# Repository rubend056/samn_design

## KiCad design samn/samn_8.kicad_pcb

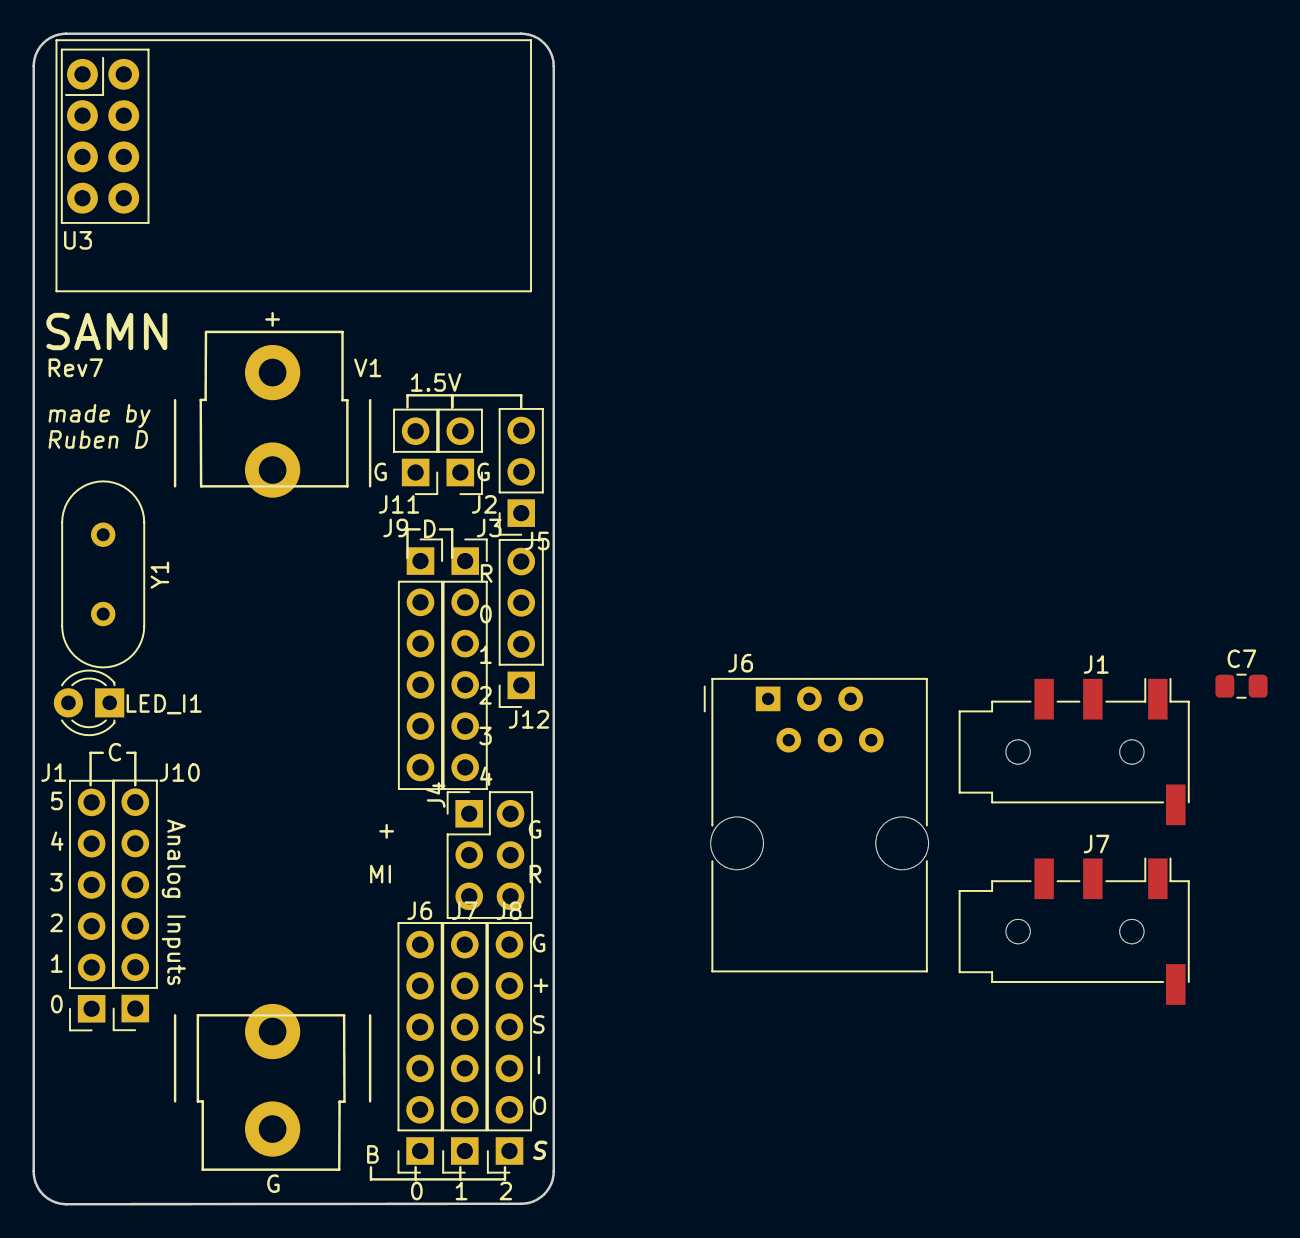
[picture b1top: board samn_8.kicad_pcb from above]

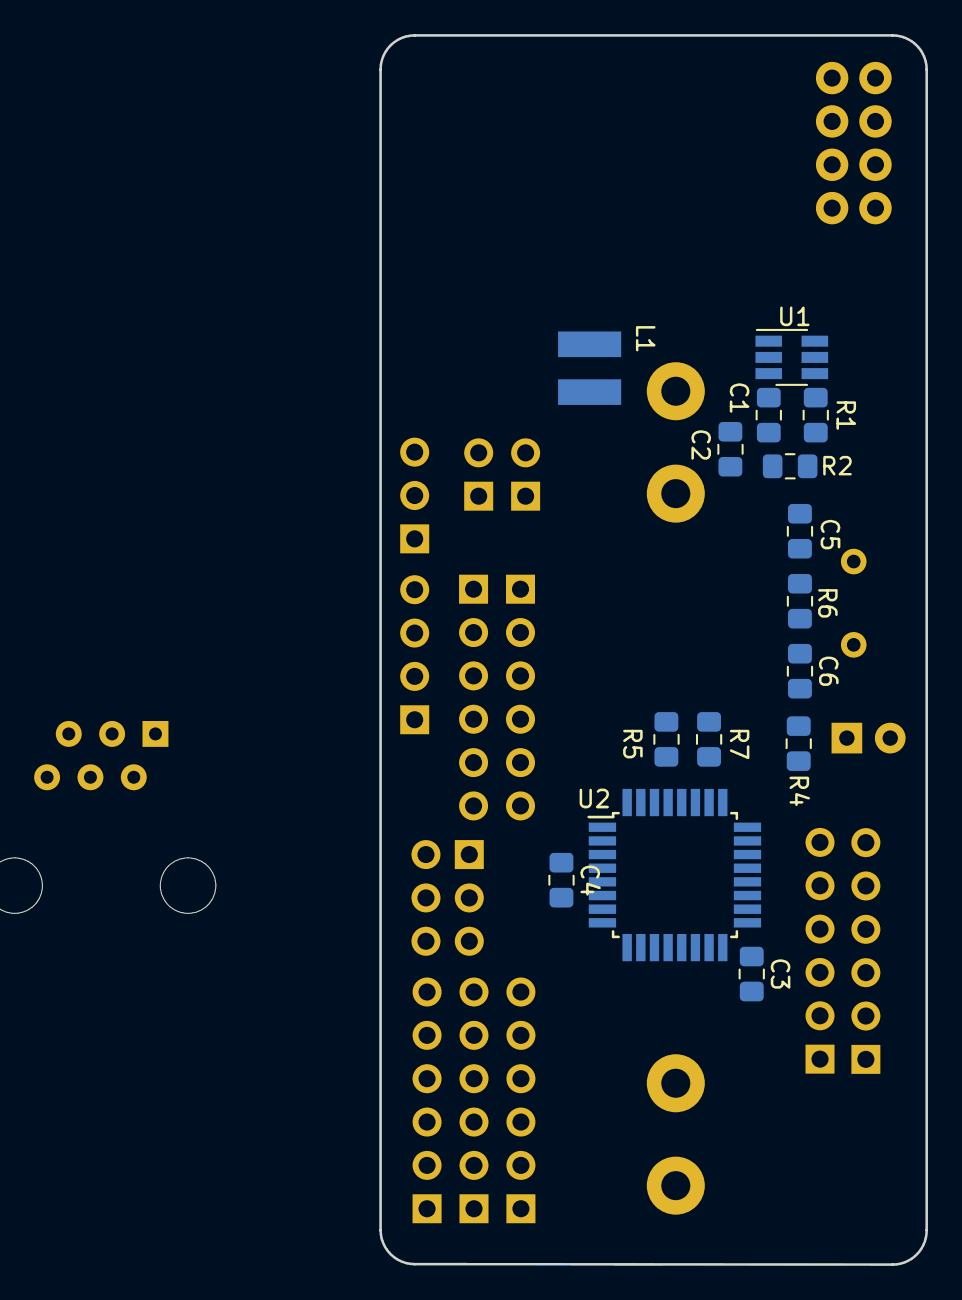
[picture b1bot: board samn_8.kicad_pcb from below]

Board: 2 copper layers, 32.0 x 72.0 mm, 35 parts (15 on the bottom side), 34 nets, no tracks yet.

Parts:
C1: 4.7uF; C_0805_2012Metric_Pad1.15x1.40mm_HandSolder
C2: 10uF; C_0805_2012Metric_Pad1.15x1.40mm_HandSolder
C3, C5, C6: 22pF; C_0805_2012Metric_Pad1.15x1.40mm_HandSolder
C4, C7: 100uF; C_0805_2012Metric_Pad1.15x1.40mm_HandSolder
J1, J7: AudioJack4; Jack_3.5mm_PJ320D_Horizontal
J1#2, J3, J9, J10: Conn_01x06_Female; PinSocket_1x06_P2.54mm_Vertical
J2, J11: Conn_01x02; PinHeader_1x02_P2.54mm_Vertical
J4: Conn_02x03_Male_ICSP; PinHeader_2x03_P2.54mm_Vertical
J5: Conn_01x03; PinSocket_1x03_P2.54mm_Vertical
J6: 6P6C; RJ12_Amphenol_54601
J6#2, J7#2, J8: Conn_01x06; PinSocket_1x06_P2.54mm_Vertical
J12: Conn_01x04; PinSocket_1x04_P2.54mm_Vertical
L1: 4.7uH; NRS4018T4R7MDGJ
LED_I1: 2V 20mA; LED_D3.0mm_FlatTop
R1: 976k; R_0805_2012Metric_Pad1.15x1.40mm_HandSolder
R2: 576k; R_0805_2012Metric_Pad1.15x1.40mm_HandSolder
R4: 200; R_0805_2012Metric_Pad1.15x1.40mm_HandSolder
R5: 5.1k; R_0805_2012Metric_Pad1.15x1.40mm_HandSolder
R6: 1M; R_0805_2012Metric_Pad1.15x1.40mm_HandSolder
R7: 10k; R_0805_2012Metric_Pad1.15x1.40mm_HandSolder
U1: MCP1640BCH; SOT-23-6_Handsoldering
U2: ATmega328PB-AU; TQFP-32_7x7mm_P0.8mm
U3: NRF24L01_Breakout; nRF24L01_Breakout_mine
V1: AA; AA_Holder
Y1: 8MHz; Crystal_HC49-4H_Vertical

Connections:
+1V5: C1.1, J5.2, L1.1, R7.2, U1.3, U1.6
+3V3: C2.2, C4.1, C7.1, J4.5, J6.2, J6#2.5, J7#2.5, J8.5, R1.1, R5.1, U1.5, U2.4, U2.18, U3.2
GND: C1.2, C2.1, C3.1, C4.2, C5.2, C6.2, C7.2, J2.1, J4.1, J6.1, J6#2.6, J7#2.6, J8.6, J11.1, LED_I1.1, R2.2, U1.2, U2.5, U2.21, U3.1, V1.2
MISO: J4.6, J6.4, J6#2.3, J7#2.3, J8.3, U2.16, U3.7
MOSI: J4.3, J6.3, J6#2.2, J7#2.2, J8.2, U2.15, U3.6
unnamed: C3.2, U2.20
unnamed: C5.1, R6.1, U2.7, Y1.1
unnamed: C6.1, R6.2, U2.8, Y1.2
unnamed: J1#2.1, J10.1
unnamed: J1#2.2, J10.2
unnamed: J1#2.3, J10.3
unnamed: J1#2.4, J10.4
unnamed: J1#2.5, J10.5
unnamed: J1#2.6, J10.6
unnamed: J3.2, J9.2, U2.30
unnamed: J3.3, J9.3, U2.31
unnamed: J3.4, J9.4, U2.32, U3.8
unnamed: J3.5, J9.5, U2.1
unnamed: J3.6, J9.6, U2.2
unnamed: J6.6, U2.14
unnamed: J2.2, J5.3, J11.2, V1.1
unnamed: J12.1, U2.22
unnamed: J12.2, U2.19
unnamed: J12.3, U2.6
unnamed: J12.4, U2.3
unnamed: L1.2, U1.1
unnamed: LED_I1.2, R4.1
unnamed: R1.2, R2.1, U1.4
unnamed: R4.2, U2.9
unnamed: R7.1, U2.26
unnamed: U2.10, U3.3
unnamed: U2.11, U3.4
Reset: J3.1, J4.2, J9.1, R5.2, U2.29
SCK: J4.4, J6.5, J6#2.4, J7#2.4, J8.4, U2.17, U3.5

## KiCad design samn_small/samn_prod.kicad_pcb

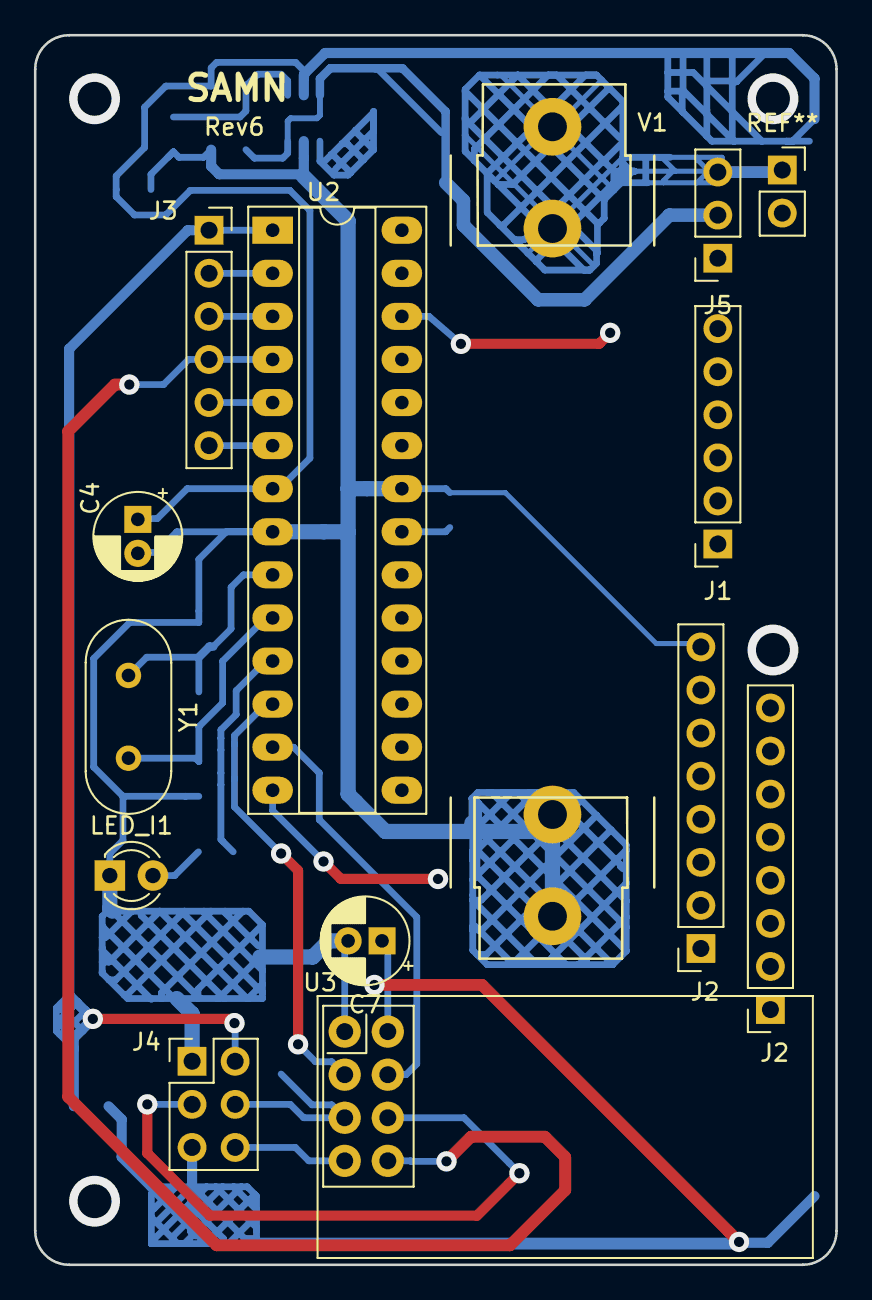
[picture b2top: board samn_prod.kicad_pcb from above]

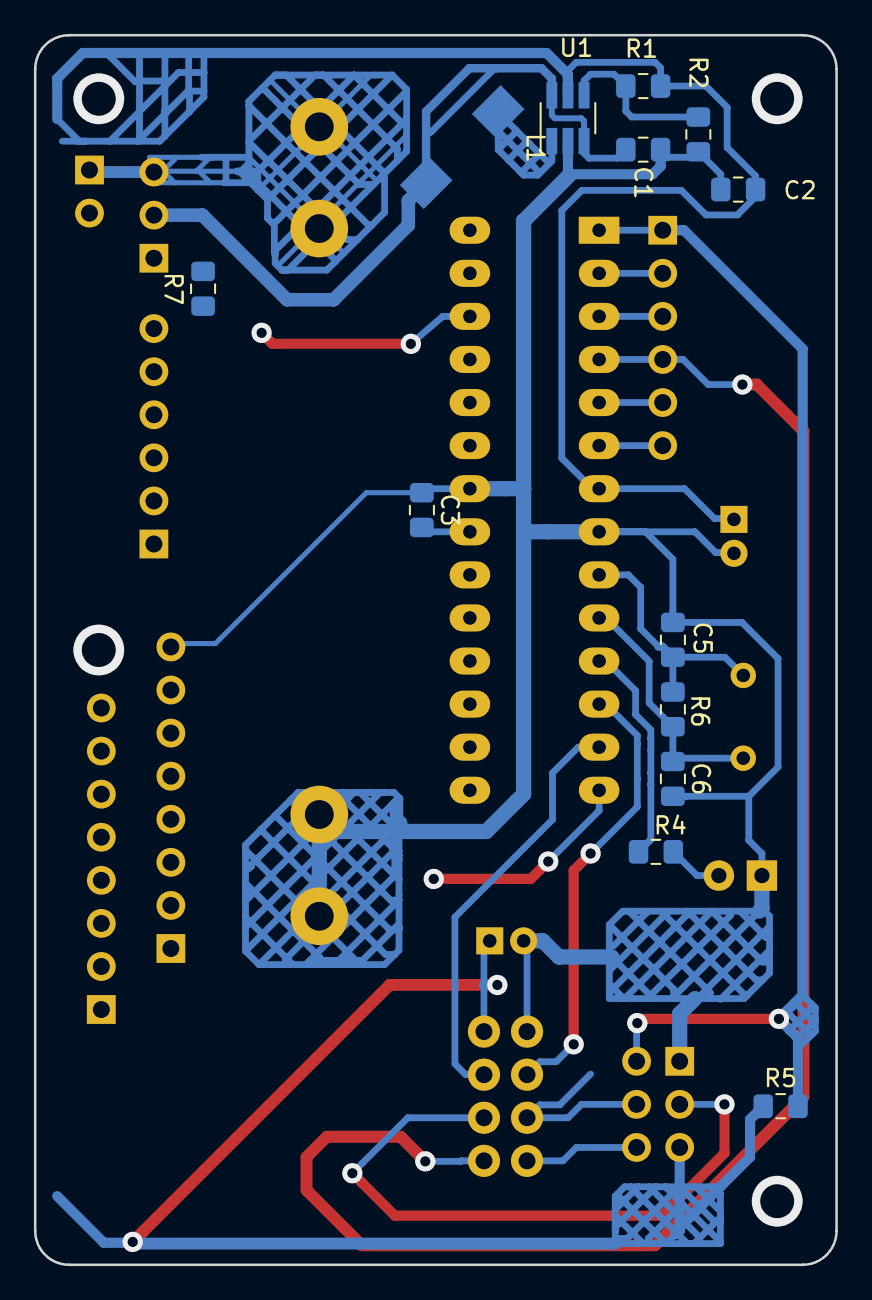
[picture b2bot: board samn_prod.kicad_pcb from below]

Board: 2 copper layers, 47.2 x 72.5 mm, 26 parts (13 on the bottom side), 31 nets.

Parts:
C1: 4.7uF; C_0805_2012Metric_Pad1.15x1.40mm_HandSolder
C2: 10uF; C_0805_2012Metric_Pad1.15x1.40mm_HandSolder
C3, C5, C6: 22pF; C_0805_2012Metric_Pad1.15x1.40mm_HandSolder
C4: 100uF; CP_Radial_D5.0mm_P2.00mm
C7: 47uF; CP_Radial_D5.0mm_P2.00mm
J1, J3: Conn_01x06_Female; PinSocket_1x06_P2.54mm_Vertical
J2, J2#2: Conn_01x08_Female; PinSocket_1x08_P2.54mm_Vertical
J4: Conn_02x03_Male_ICSP; PinHeader_2x03_P2.54mm_Vertical
J5: Conn_01x03; PinSocket_1x03_P2.54mm_Vertical
L1: 4.7uH; SWRH3D16R-4R7NT
LED_I1: 2V 20mA; LED_D3.0mm_FlatTop
R1: 976k; R_0805_2012Metric_Pad1.15x1.40mm_HandSolder
R2: 576k; R_0805_2012Metric_Pad1.15x1.40mm_HandSolder
R4: 200; R_0805_2012Metric_Pad1.15x1.40mm_HandSolder
R5: 5.1k; R_0805_2012Metric_Pad1.15x1.40mm_HandSolder
R6: 1M; R_0805_2012Metric_Pad1.15x1.40mm_HandSolder
R7: 10k; R_0805_2012Metric_Pad1.15x1.40mm_HandSolder
U1: MCP1640BCH; SOT-23-6_Handsoldering
U2: ATmega328-PU; DIP-28_W7.62mm_Socket_LongPads
U3: NRF24L01_Breakout; nRF24L01_Breakout_mine
V1: AA; AA_Holder
Y1: 8MHz; Crystal_HC49-4H_Vertical

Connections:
+1V5: C1.1, J5.2, L1.1, R7.2, U1.3, U1.6
+3V3: C2.2, C4.1, C7.1, J2#2.7, J4.5, R1.1, R5.1, U1.5, U2.7, U2.20, U3.2
GND: C1.2, C2.1, C3.1, C4.2, C5.2, C6.2, C7.2, J2#2.8, J4.1, J5.1, LED_I1.1, R2.2, U1.2, U2.8, U2.22, U3.1, V1.2
MISO: J2#2.5, J4.6, U2.18, U3.7
MOSI: J2#2.4, J4.3, U2.17, U3.6
unnamed: C3.2, U2.21
unnamed: C5.1, R6.1, U2.9, Y1.1
unnamed: C6.1, R6.2, U2.10, Y1.2
unnamed: J1.1, U2.23
unnamed: J1.2, U2.24
unnamed: J1.3, U2.25
unnamed: J1.5, U2.27
unnamed: J1.6, U2.28
unnamed: J2#2.1, U2.14
unnamed: J2#2.2, U2.15
unnamed: J2#2.3, U2.16
unnamed: J3.2, U2.2
unnamed: J3.3, U2.3
unnamed: J3.4, U2.4, U3.8
unnamed: J3.5, U2.5
unnamed: J3.6, U2.6
unnamed: J5.3, V1.1
unnamed: L1.2, U1.1
unnamed: LED_I1.2, R4.1
unnamed: R1.2, R2.1, U1.4
unnamed: R4.2, U2.11
unnamed: R7.1, U2.26
unnamed: U2.12, U3.3
unnamed: U2.13, U3.4
Reset: J3.1, J4.2, R5.2, U2.1
SCK: J2#2.6, J4.4, U2.19, U3.5

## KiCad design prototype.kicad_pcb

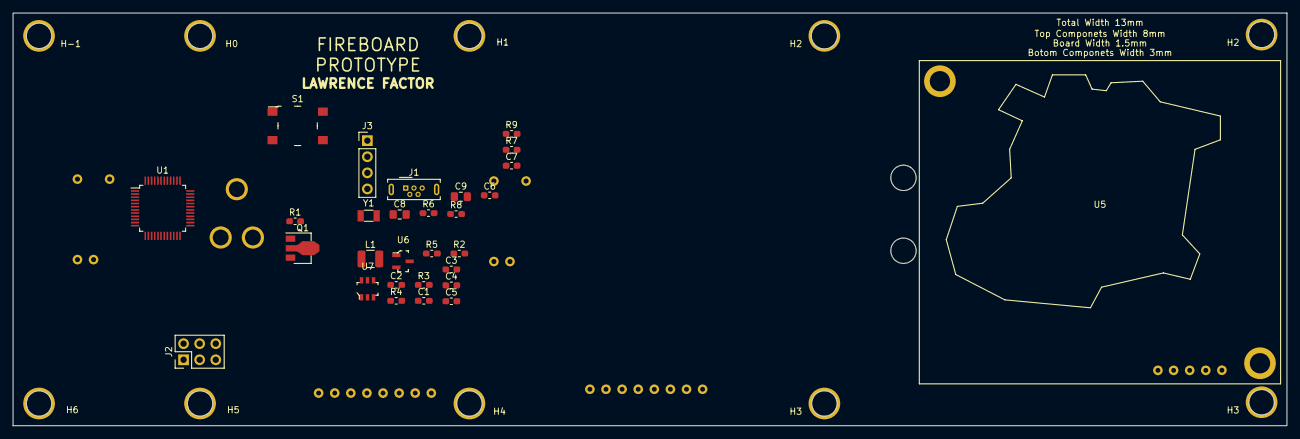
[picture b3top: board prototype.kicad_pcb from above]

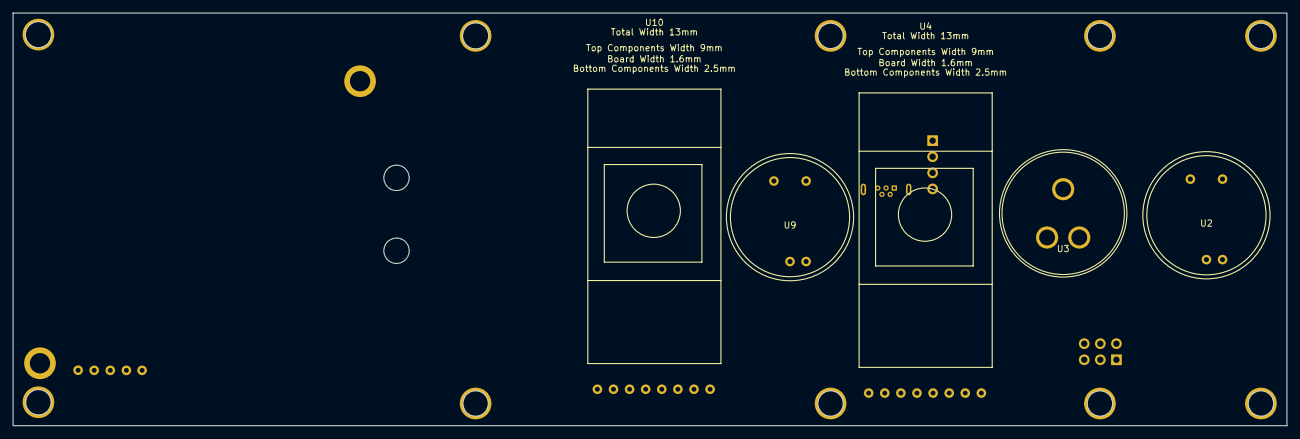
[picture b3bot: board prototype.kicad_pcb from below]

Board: 2 copper layers, 201.0 x 65.1 mm, 44 parts (5 on the bottom side), 32 nets, no tracks yet.

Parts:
C1: 1uF 5V; C_0603_1608Metric_Pad1.05x0.95mm_HandSolder
C2: 10uF 12V; C_0603_1608Metric_Pad1.05x0.95mm_HandSolder
C3: 1uF 3.3V; C_0603_1608Metric_Pad1.05x0.95mm_HandSolder
C4: 10nF 5V; C_0603_1608Metric_Pad1.05x0.95mm_HandSolder
C5: 22uF 5V; C_0603_1608Metric_Pad1.05x0.95mm_HandSolder
C6, C7: 12.5pF; C_0603_1608Metric_Pad1.05x0.95mm_HandSolder
C8, C9: 10uF; C_0805_2012Metric_Pad1.15x1.40mm_HandSolder
H0, H1, H2, H2#2, H3, H3#2, H4, H5, H6: 4mm_hole
H-1: 4mm_hole
J1: USB_B_Micro; USB_Micro-B_Wuerth_614105150721_Vertical
J2: Conn_02x03_Odd_Even; PinHeader_2x03_P2.54mm_Vertical
J3: Link; PinHeader_1x04_P2.54mm_Vertical
L1: 4.7uH; L_1210_3225Metric
Q1: Q_NPN_BCE; SOT-89-3
R1: 330R; R_0603_1608Metric_Pad1.05x0.95mm_HandSolder
R2: 200k; R_0603_1608Metric_Pad1.05x0.95mm_HandSolder
R3: 510k; R_0603_1608Metric_Pad1.05x0.95mm_HandSolder
R4: 47k; R_0603_1608Metric_Pad1.05x0.95mm_HandSolder
R5: 33k; R_0603_1608Metric_Pad1.05x0.95mm_HandSolder
R6, R7: 4.7k; R_0603_1608Metric_Pad1.05x0.95mm_HandSolder
R8: 10k; R_0603_1608Metric_Pad1.05x0.95mm_HandSolder
R9: 22R; R_0603_1608Metric_Pad1.05x0.95mm_HandSolder
S1: KS-01Q-01; Switch_Tactile_SMD_6x6mm_PTS645
U1: ATSAMD21G18A-AUT; TQFP-48_7x7mm_P0.5mm
U2, U9: LOX-02-S
U3: PID-AH
U4, U10: CO
U5: CO2
U6: 3.3V; SOT-23-3
U7: AP3211 Buck; SOT-23-6
Y1: 32.86MHz; Crystal_SMD_3215-2Pin_3.2x1.5mm

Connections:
+5V: C1.1, C5.1, J1.1, J2.2, L1.2, U2.1, U3.1, U6.2, U9.1
+12V: C2.1, J3.2, R3.1, U5.3, U7.5
/PIDGND: Q1.2, U3.3
/PID_on: R1.2, U1.13
/RX0: U1.16, U9.3
/RX1: U1.28, U10.3
/RX2: U1.24, U2.3
/RX3: U1.30, U4.3
/TX0: U1.15, U9.4
/TX1: U1.27, U10.2
/TX2: U1.23, U2.4
/TX3: U1.29, U4.2
D+: J1.3, U1.34
D-: J1.2, U1.33
GND: C1.2, C2.2, C3.2, C5.2, C6.2, C7.2, C8.1, C9.1, J1.5, J1.6, J2.6, J3.1, Q1.3, R2.1, R5.2, S1.2, S1.4, U1.5, U1.18, U1.35, U1.42, U2.2, U4.6, U5.2, U6.1, U7.2, U9.2, U10.6
MISO: J2.1, U1.21
MOSI: J2.4, U1.19
unnamed: C4.1, U7.1
unnamed: C4.2, L1.1, R4.1, U7.6
unnamed: Q1.1, R1.1
unnamed: R2.2, R3.2, U7.4
unnamed: R4.2, R5.1, U7.3
unnamed: R9.2, S1.1, S1.3
PA02_AIN0: U1.3, U3.2
SAMD_Reset: J2.5, R8.2, R9.1, U1.40
SCK: J2.3, U1.20
SCL: J3.4, R7.2, U1.32, U5.4
SDA: J3.3, R6.2, U1.31, U5.5
VDDANA: C3.1, C8.2, R6.1, R7.1, R8.1, U1.6, U1.17, U1.36, U1.44, U4.8, U5.1, U6.3, U10.8
VDDCORE: C9.2, U1.43
XTAL0: C6.1, U1.1, Y1.1
XTAL1: C7.1, U1.2, Y1.2

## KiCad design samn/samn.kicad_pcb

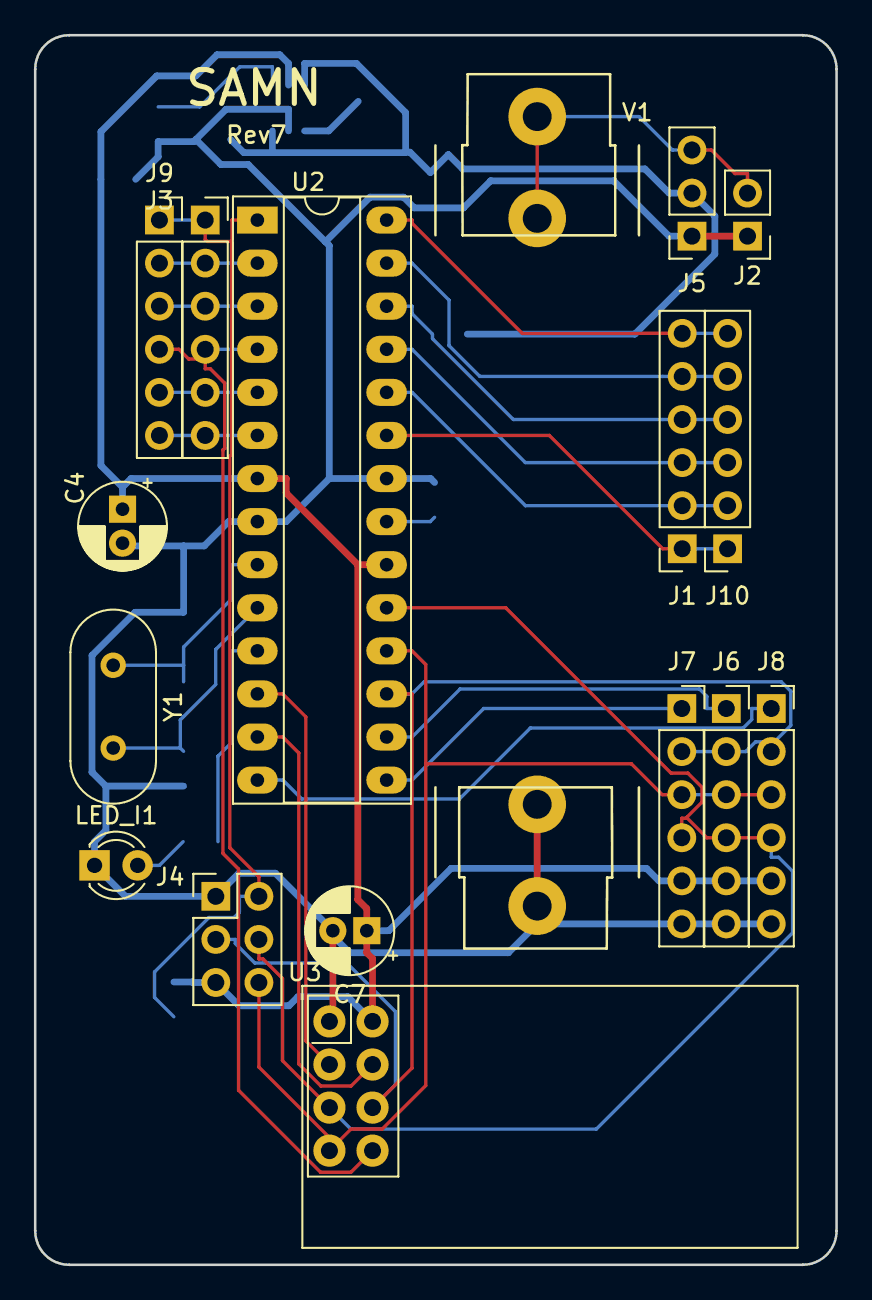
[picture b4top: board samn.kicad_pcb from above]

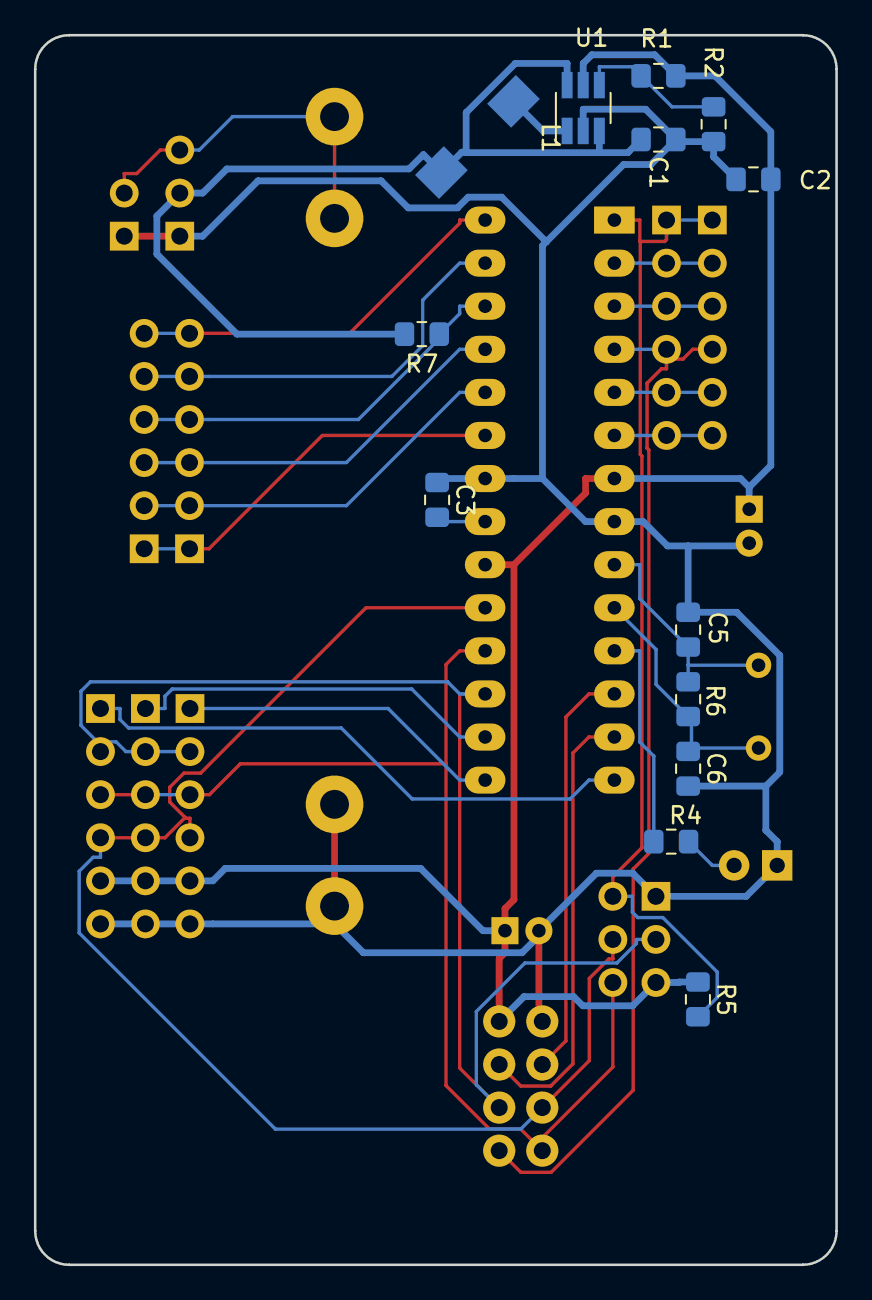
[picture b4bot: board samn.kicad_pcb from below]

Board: 2 copper layers, 47.2 x 72.5 mm, 30 parts (13 on the bottom side), 31 nets.

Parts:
C1: 4.7uF; C_0805_2012Metric_Pad1.15x1.40mm_HandSolder
C2: 10uF; C_0805_2012Metric_Pad1.15x1.40mm_HandSolder
C3, C5, C6: 22pF; C_0805_2012Metric_Pad1.15x1.40mm_HandSolder
C4: 100uF; CP_Radial_D5.0mm_P2.00mm
C7: 47uF; CP_Radial_D5.0mm_P2.00mm
J1, J3, J9, J10: Conn_01x06_Female; PinSocket_1x06_P2.54mm_Vertical
J2: Conn_01x02; PinHeader_1x02_P2.54mm_Vertical
J4: Conn_02x03_Male_ICSP; PinHeader_2x03_P2.54mm_Vertical
J5: Conn_01x03; PinSocket_1x03_P2.54mm_Vertical
J6, J7, J8: Conn_01x06; PinSocket_1x06_P2.54mm_Vertical
L1: 4.7uH; SWRH3D16R-4R7NT
LED_I1: 2V 20mA; LED_D3.0mm_FlatTop
R1: 976k; R_0805_2012Metric_Pad1.15x1.40mm_HandSolder
R2: 576k; R_0805_2012Metric_Pad1.15x1.40mm_HandSolder
R4: 200; R_0805_2012Metric_Pad1.15x1.40mm_HandSolder
R5: 5.1k; R_0805_2012Metric_Pad1.15x1.40mm_HandSolder
R6: 1M; R_0805_2012Metric_Pad1.15x1.40mm_HandSolder
R7: 10k; R_0805_2012Metric_Pad1.15x1.40mm_HandSolder
U1: MCP1640BCH; SOT-23-6_Handsoldering
U2: ATmega328-PU; DIP-28_W7.62mm_Socket_LongPads
U3: NRF24L01_Breakout; nRF24L01_Breakout_mine
V1: AA; AA_Holder
Y1: 8MHz; Crystal_HC49-4H_Vertical

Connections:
+1V5: C1.1, J5.2, L1.1, R7.2, U1.3, U1.6
+3V3: C2.2, C4.1, C7.1, J4.5, J6.5, J7.5, J8.5, R1.1, R5.1, U1.5, U2.7, U2.20, U3.2
GND: C1.2, C2.1, C3.1, C4.2, C5.2, C6.2, C7.2, J2.1, J4.1, J5.1, J6.6, J7.6, J8.6, LED_I1.1, R2.2, U1.2, U2.8, U2.22, U3.1, V1.2
MISO: J4.6, J6.3, J7.3, J8.3, U2.18, U3.7
MOSI: J4.3, J6.2, J7.2, J8.2, U2.17, U3.6
unnamed: C3.2, U2.21
unnamed: C5.1, R6.1, U2.9, Y1.1
unnamed: C6.1, R6.2, U2.10, Y1.2
unnamed: J1.1, J10.1, U2.23
unnamed: J1.2, J10.2, U2.24
unnamed: J1.3, J10.3, U2.25
unnamed: J1.4, J10.4, R7.1, U2.26
unnamed: J1.5, J10.5, U2.27
unnamed: J1.6, J10.6, U2.28
unnamed: J2.2, J5.3, V1.1
unnamed: J3.2, J9.2, U2.2
unnamed: J3.3, J9.3, U2.3
unnamed: J3.4, J9.4, U2.4, U3.8
unnamed: J3.5, J9.5, U2.5
unnamed: J3.6, J9.6, U2.6
unnamed: J6.1, U2.16
unnamed: J7.1, U2.15
unnamed: J8.1, U2.14
unnamed: L1.2, U1.1
unnamed: LED_I1.2, R4.1
unnamed: R1.2, R2.1, U1.4
unnamed: R4.2, U2.11
unnamed: U2.12, U3.3
unnamed: U2.13, U3.4
Reset: J3.1, J4.2, J9.1, R5.2, U2.1
SCK: J4.4, J6.4, J7.4, J8.4, U2.19, U3.5

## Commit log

2019-12-31 staring v8 of samn
2019-12-31 adding kicad lib
